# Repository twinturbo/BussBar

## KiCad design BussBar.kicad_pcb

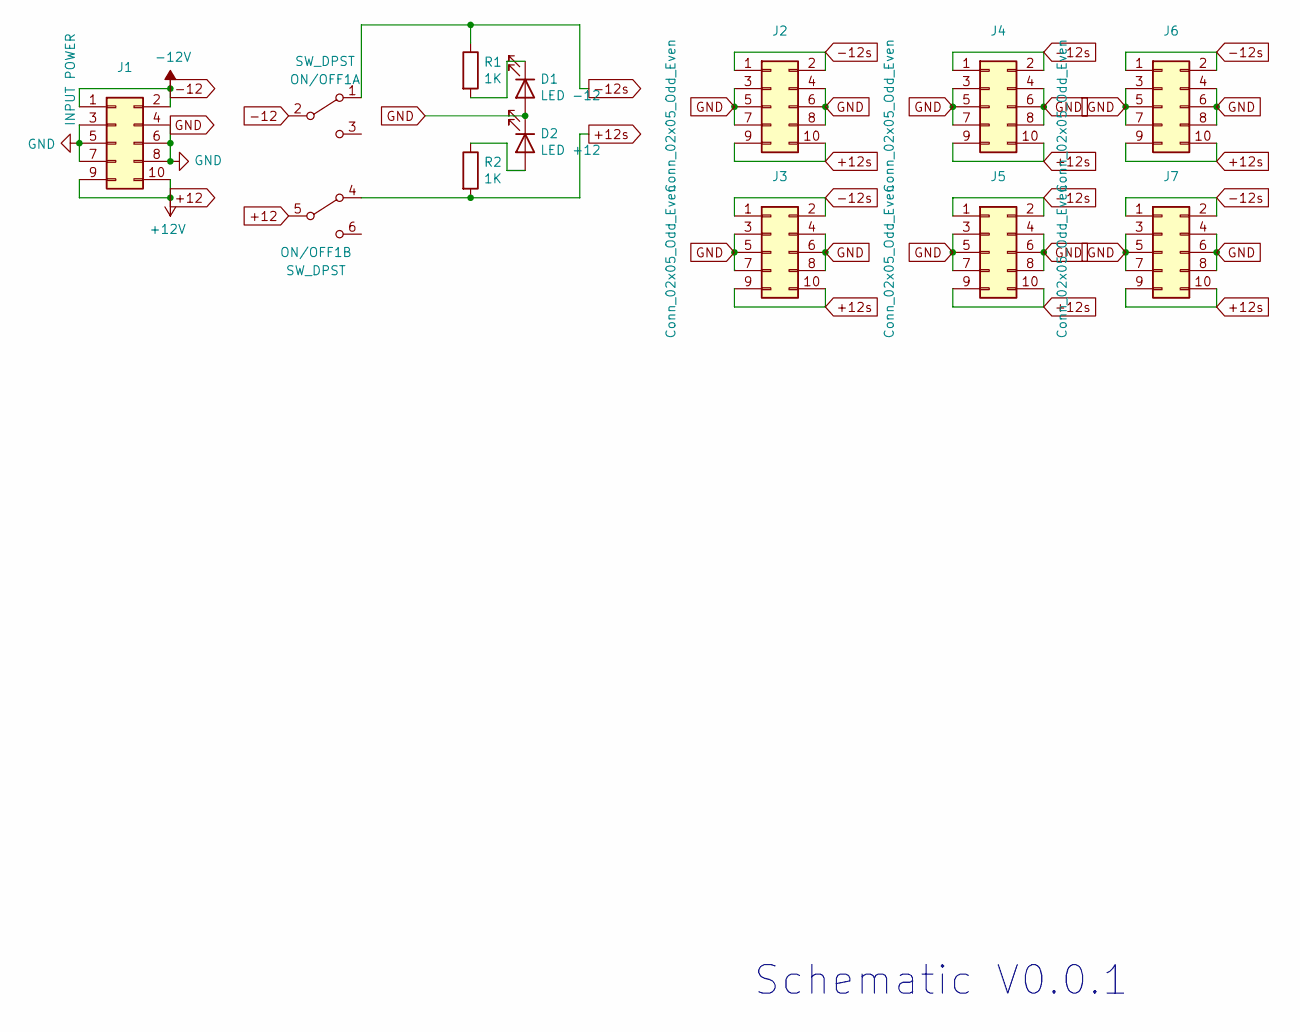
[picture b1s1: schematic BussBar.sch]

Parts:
D1: LED -12; LED_D5.0mm
D2: LED +12; LED_D5.0mm
J1: INPUT POWER; IDC-Header_2x05_P2.54mm_Vertical
J2, J3, J4, J5, J6, J7: Conn_02x05_Odd_Even; IDC-Header_2x05_P2.54mm_Vertical
ON/OFF1: SW_DPST; SW_CK_Lever_DPDT_72xx_CircularHoles
R1, R2: 1K; R_Axial_DIN0204_L3.6mm_D1.6mm_P5.08mm_Horizontal

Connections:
+12: J1.9, J1.10, ON/OFF1.5 (B)
+12s: J2.9, J2.10, J3.9, J3.10, J4.9, J4.10, J5.9, J5.10, J6.9, J6.10, J7.9, J7.10, ON/OFF1.4 (A), R2.2
-12: J1.1, J1.2, ON/OFF1.2 (B)
-12s: J2.1, J2.2, J3.1, J3.2, J4.1, J4.2, J5.1, J5.2, J6.1, J6.2, J7.1, J7.2, ON/OFF1.1 (A), R1.1
GND: D1.2 (A), D2.1 (K), J1.3, J1.4, J1.5, J1.6, J1.7, J1.8, J2.3, J2.4, J2.5, J2.6, J2.7, J2.8, J3.3, J3.4, J3.5, J3.6, J3.7, J3.8, J4.3, J4.4, J4.5, J4.6, J4.7, J4.8, J5.3, J5.4, J5.5, J5.6, J5.7, J5.8, J6.3, J6.4, J6.5, J6.6, J6.7, J6.8, J7.3, J7.4, J7.5, J7.6, J7.7, J7.8; also elsewhere on the board
unnamed: D1.1 (K), R1.2
unnamed: D2.2 (A), R2.1

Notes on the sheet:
Schematic V0.0.1

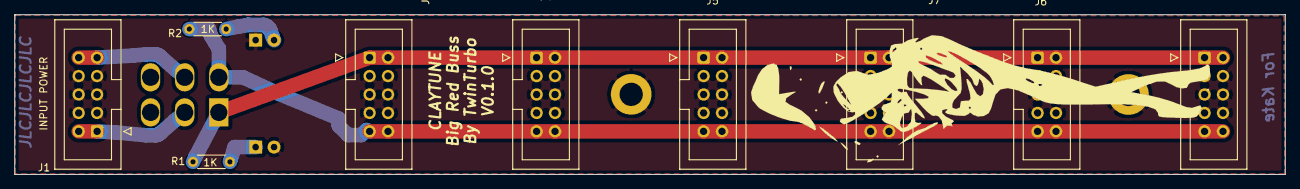
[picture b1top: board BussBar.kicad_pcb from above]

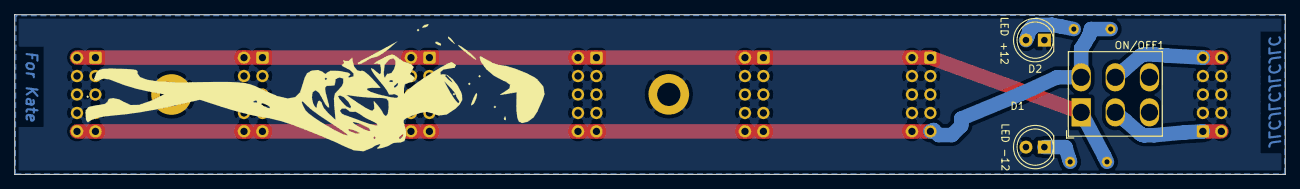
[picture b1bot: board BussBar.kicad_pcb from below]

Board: 2 copper layers, 175.0 x 22.0 mm, 16 parts (4 on the bottom side), 7 nets.

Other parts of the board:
GIJO, GIJO1: LOGO; Girl7
H1, H2: MountingHole_Pad; MountingHole_3.2mm_M3_DIN965_Pad

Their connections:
GND: H1.1, H2.1; also elsewhere on the board

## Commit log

2020-12-23 autosync
2020-12-23 Initialised
2020-12-23 Clean
2020-12-23 Initial Schematic V0.0.1
2020-12-23 V0.0.1 Chematic and PCB - Initial to routing
2020-12-24 Standof and FP Started
2020-12-24 New Mounting Holes
2020-12-24 FP Boards Aligned
2020-12-24 FP Holes Added
2020-12-24 FP Labels
2020-12-24 Filled - netted
2020-12-25 Board/FP ready
2020-12-25 ChangeLog/VerLog Updated
2021-01-21 Log Update
2022-02-07 Fixup
